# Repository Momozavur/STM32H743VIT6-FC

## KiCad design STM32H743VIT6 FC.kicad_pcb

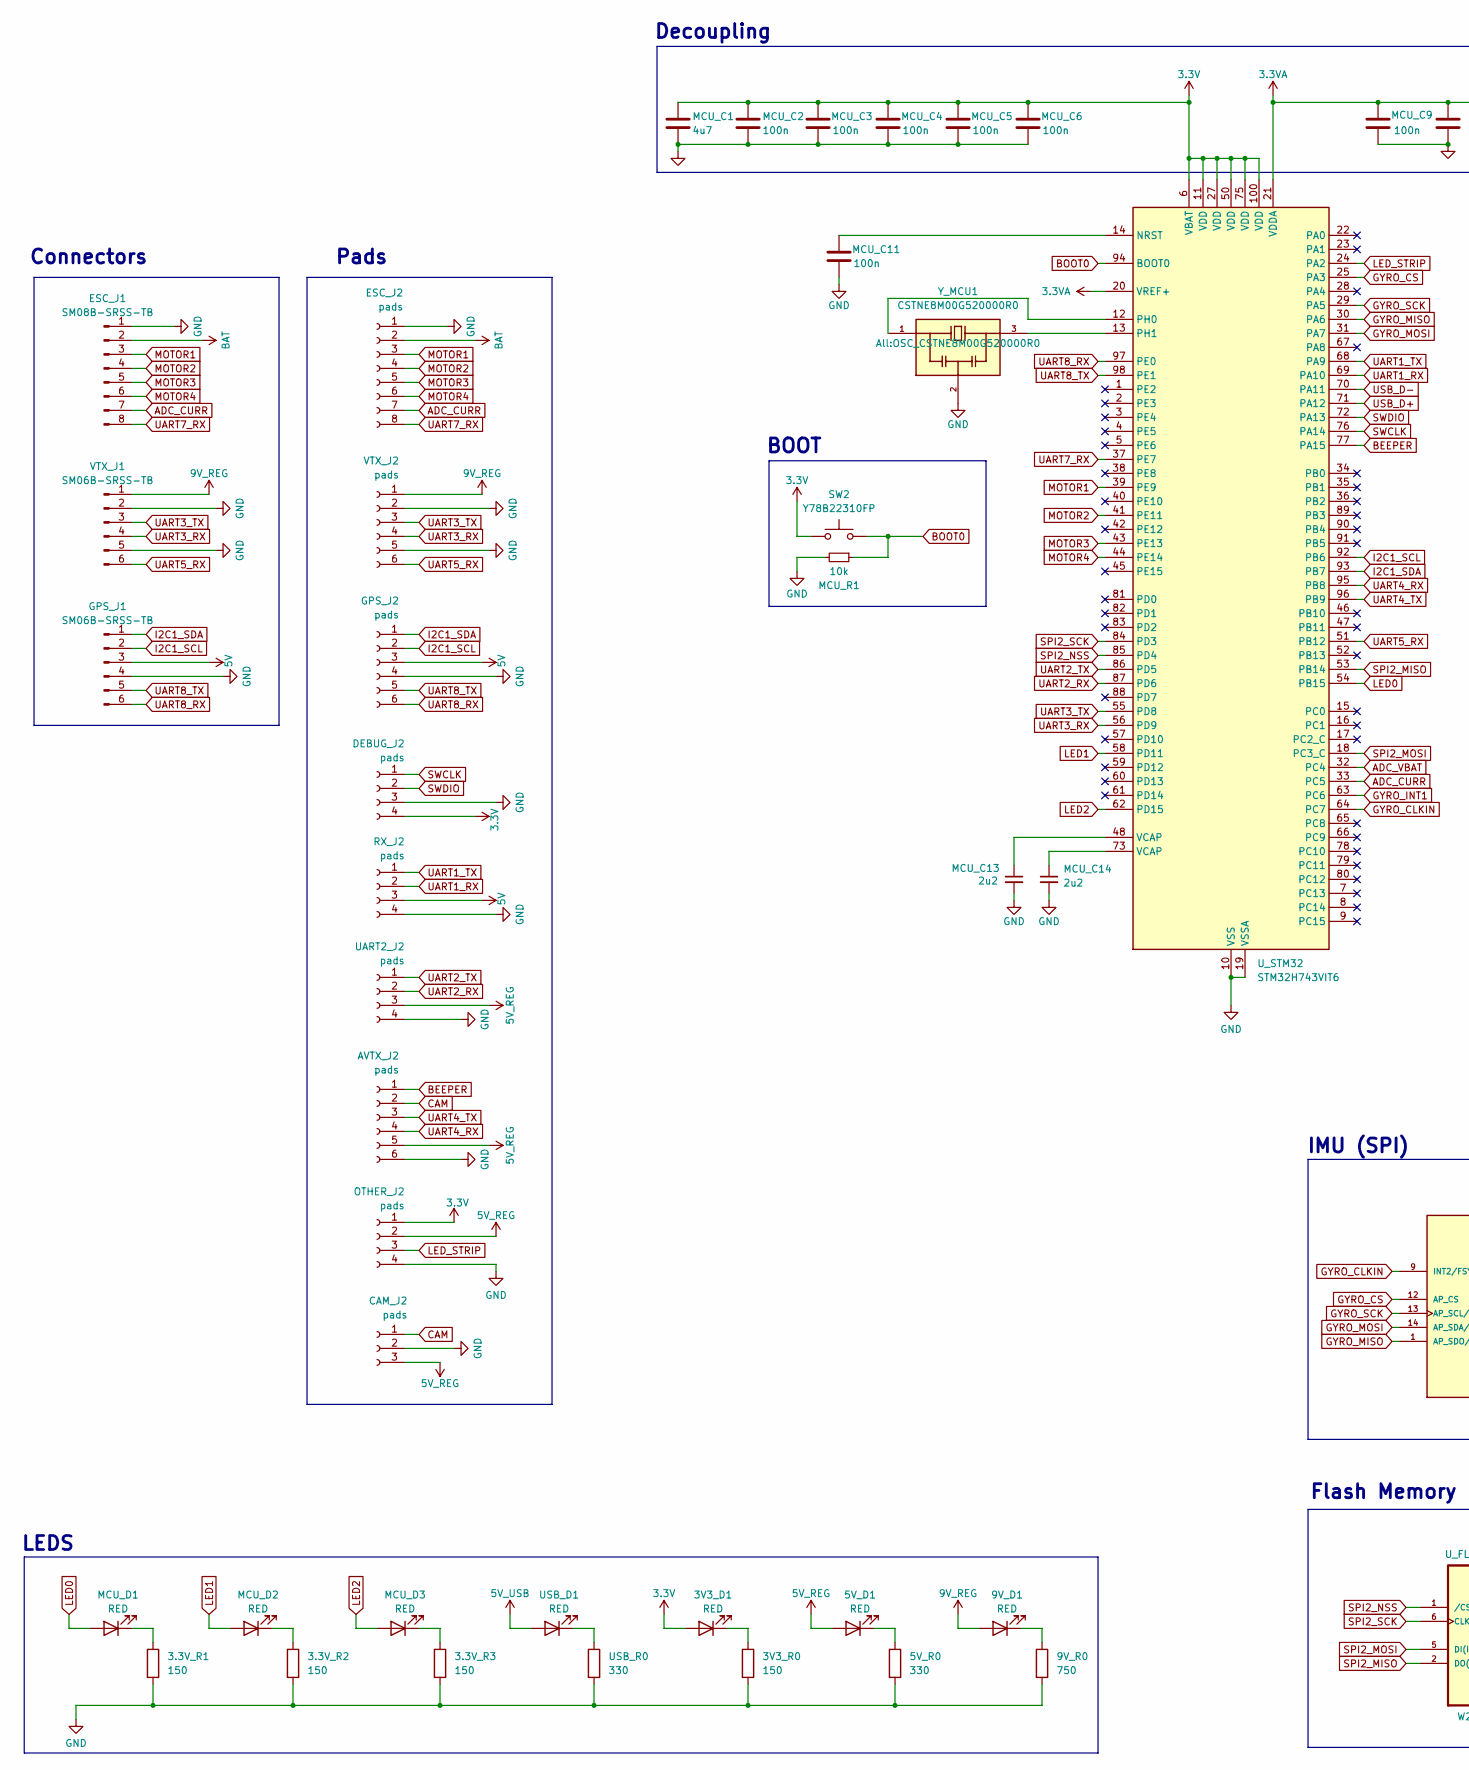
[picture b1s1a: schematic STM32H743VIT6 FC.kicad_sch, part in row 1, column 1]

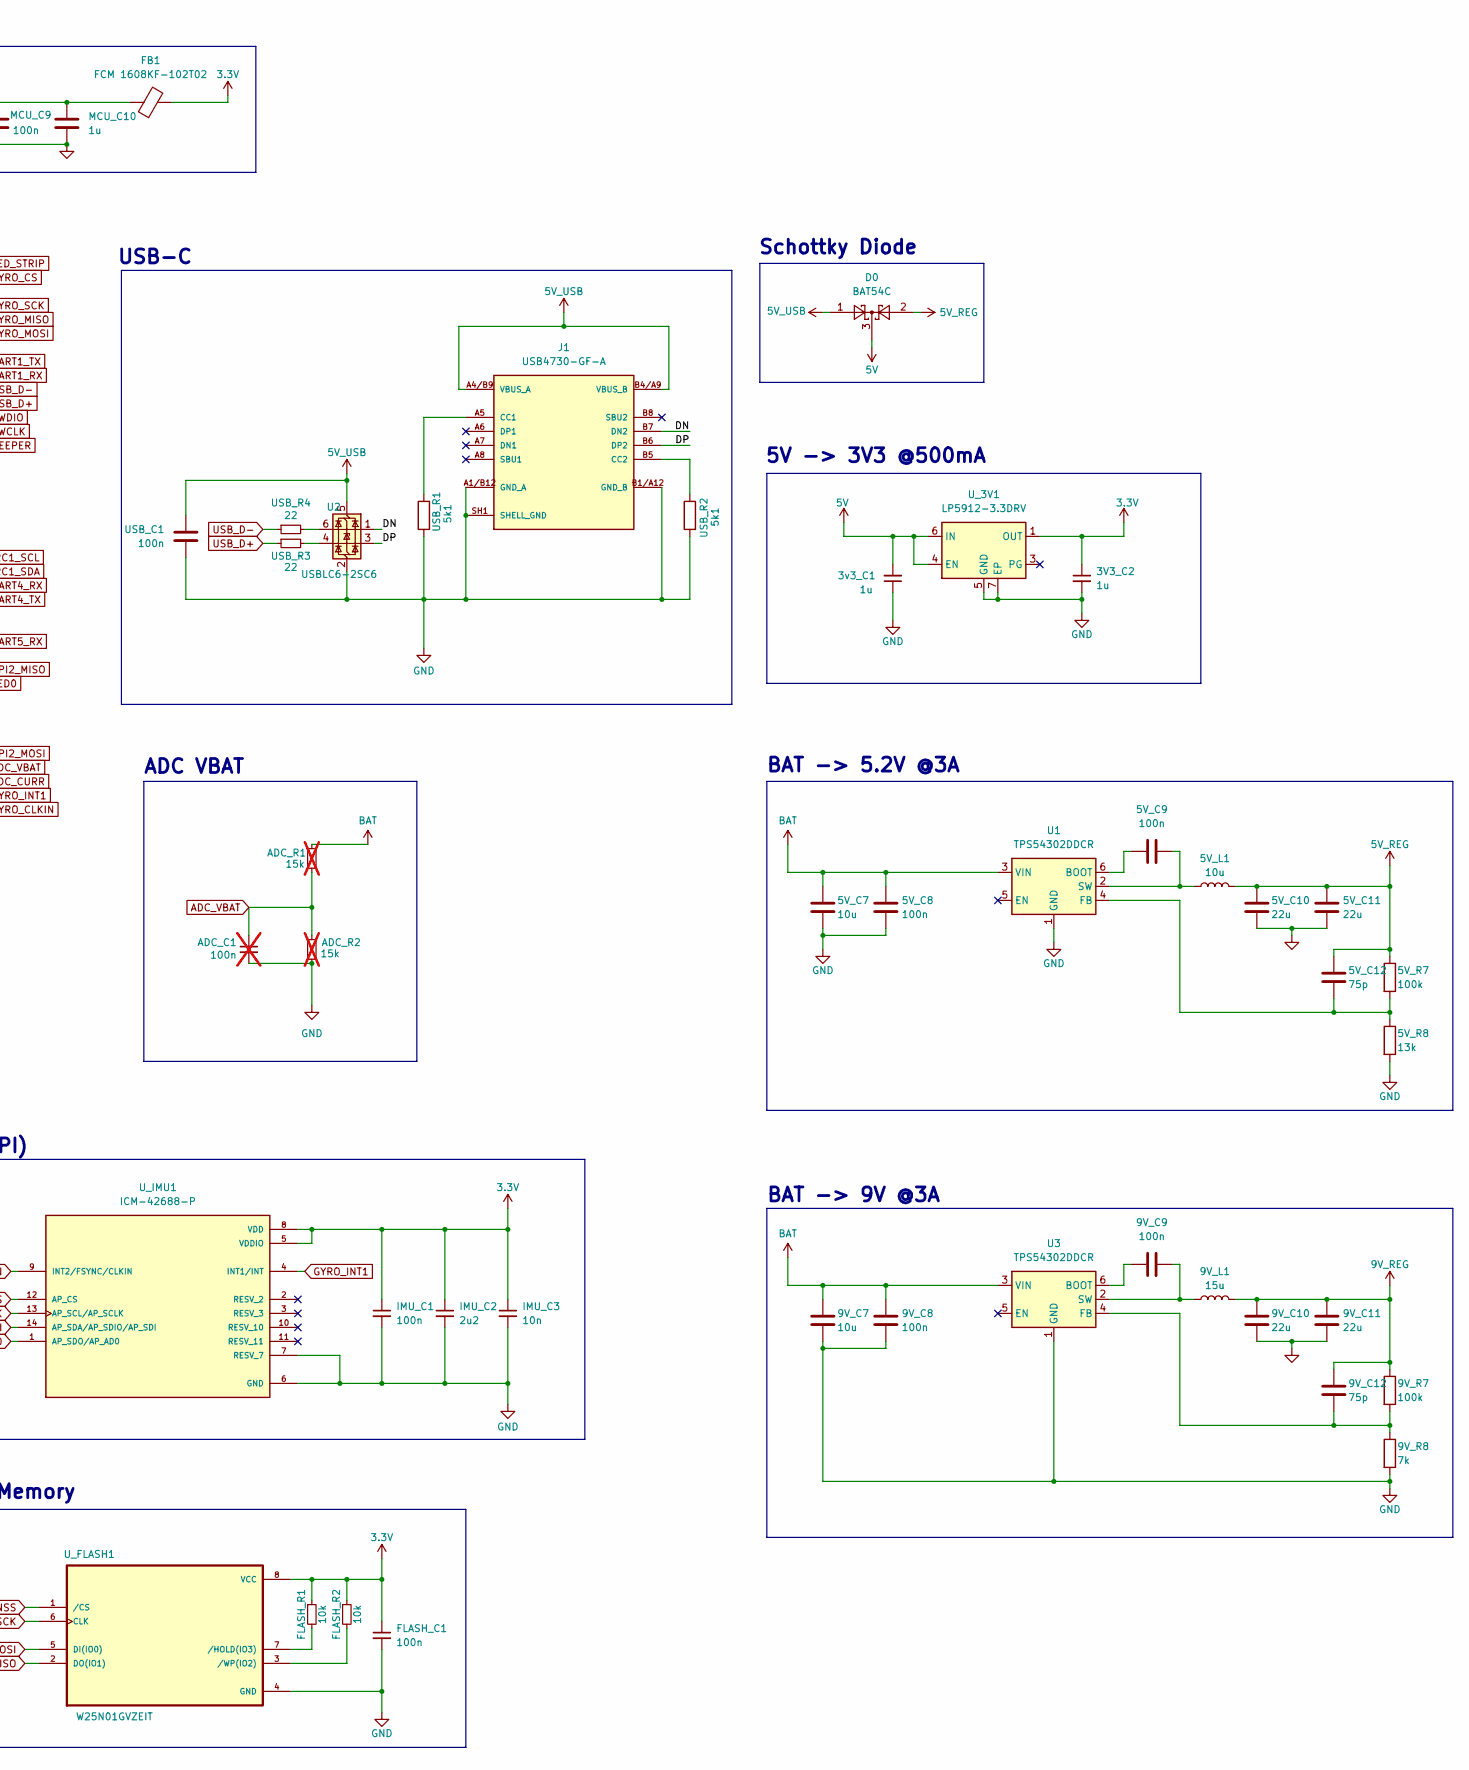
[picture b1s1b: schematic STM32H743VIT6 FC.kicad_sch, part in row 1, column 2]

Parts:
3.3V_R1, 3.3V_R2, 3.3V_R3, 3V3_R0: 150; R_0603_1608Metric_Pad0.98x0.95mm_HandSolder
3V3_C2, 3v3_C1: 1u; C_0603_1608Metric_Pad1.08x0.95mm_HandSolder
3V3_D1, 5V_D1, 9V_D1: RED; LED_0603_1608Metric_Pad1.05x0.95mm_HandSolder
5V_C7, 9V_C7: 10u; C_0603_1608Metric_Pad1.08x0.95mm_HandSolder
5V_C8, 5V_C9, 9V_C8, 9V_C9: 100n; C_0603_1608Metric_Pad1.08x0.95mm_HandSolder
5V_C10, 5V_C11, 9V_C10, 9V_C11: 22u; C_0603_1608Metric_Pad1.08x0.95mm_HandSolder
5V_C12, 9V_C12: 75p; C_0603_1608Metric_Pad1.08x0.95mm_HandSolder
5V_L1: 10u; L_Wuerth_MAPI-5030
5V_R0: 330; R_0603_1608Metric_Pad0.98x0.95mm_HandSolder
5V_R7, 9V_R7: 100k; R_0603_1608Metric_Pad0.98x0.95mm_HandSolder
5V_R8: 13k; R_0603_1608Metric_Pad0.98x0.95mm_HandSolder
9V_L1: 15u; L_Wuerth_MAPI-5030
9V_R0: 750; R_0603_1608Metric_Pad0.98x0.95mm_HandSolder
9V_R8: 7k; R_0603_1608Metric_Pad0.98x0.95mm_HandSolder
ADC_C1: 100n; C_0603_1608Metric_Pad1.08x0.95mm_HandSolder; not fitted
ADC_R1, ADC_R2: 15k; R_0603_1608Metric_Pad0.98x0.95mm_HandSolder; not fitted
AVTX_J2: pads; Pads_1x6
CAM_J2: pads; Pads_1x3
D0: BAT54C; SOT-23
DEBUG_J2: pads; Pads_1x4
ESC_J1: SM08B-SRSS-TB; SM08BSRSSTB
ESC_J2: pads; Pads_1x8
FB1: FCM 1608KF-102T02; R_0603_1608Metric_Pad0.98x0.95mm_HandSolder
FLASH_C1: 100n; C_0603_1608Metric_Pad1.08x0.95mm_HandSolder
FLASH_R1, FLASH_R2: 10k; R_0603_1608Metric_Pad0.98x0.95mm_HandSolder
GPS_J1: SM06B-SRSS-TB; SM06BSRSSTBLFSN
GPS_J2: pads; Pads_1x6
IMU_C1: 100n; C_0603_1608Metric_Pad1.08x0.95mm_HandSolder
IMU_C2: 2u2; C_0603_1608Metric_Pad1.08x0.95mm_HandSolder
IMU_C3: 10n; C_0603_1608Metric_Pad1.08x0.95mm_HandSolder
J1: USB4730-GF-A; GCT_USB4730-GF-A_REVA; PARTREV A
MCU_C1: 4u7; C_0603_1608Metric_Pad1.08x0.95mm_HandSolder
MCU_C2, MCU_C3, MCU_C4, MCU_C5, MCU_C6, MCU_C9, MCU_C11: 100n; C_0603_1608Metric_Pad1.08x0.95mm_HandSolder
MCU_C10: 1u; C_0603_1608Metric_Pad1.08x0.95mm_HandSolder; JLCPCB Part # C19666
MCU_C13, MCU_C14: 2u2; C_0603_1608Metric_Pad1.08x0.95mm_HandSolder
MCU_D1, MCU_D2, MCU_D3: RED; LED_0603_1608Metric_Pad1.05x0.95mm_HandSolder
MCU_R1: 10k; R_0603_1608Metric_Pad0.98x0.95mm_HandSolder; JLCPCB Part # C25744
OTHER_J2: pads; Pads_1x4
RX_J2: pads; Pads_1x4
SW2: Y78B22310FP; SW_SPST_PTS810; JLCPCB Part # C127488
U1, U3: TPS54302DDCR; SOT-23-6
U2: USBLC6-2SC6; SOT-23-6
UART2_J2: pads; Pads_1x4
USB_C1: 100n; C_0603_1608Metric_Pad1.08x0.95mm_HandSolder
USB_D1: RED; LED_0603_1608Metric_Pad1.05x0.95mm_HandSolder
USB_R0: 330; R_0603_1608Metric_Pad0.98x0.95mm_HandSolder
USB_R1, USB_R2: 5k1; R_0603_1608Metric_Pad0.98x0.95mm_HandSolder
USB_R3, USB_R4: 22; R_0603_1608Metric_Pad0.98x0.95mm_HandSolder
U_3V1: LP5912-3.3DRV; WSON-6-1EP_2x2mm_P0.65mm_EP1x1.6mm_ThermalVias
U_FLASH1: W25N01GVZEIT; SON127P600X800X80-9N
U_IMU1: ICM-42688-P; PQFN50P300X250X97-14N; PARTREV 1.2
U_STM32: STM32H743VIT6; LQFP-100_14x14mm_P0.5mm
VTX_J1: SM06B-SRSS-TB; SM06BSRSSTBLFSN
VTX_J2: pads; Pads_1x6
Y_MCU1: CSTNE8M00G520000R0; OSC_CSTNE8M00G520000R0; PARTREV JGC42-8858A

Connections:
3.3V: 3V3_C2.1, 3V3_D1.2 (A), DEBUG_J2.4, FB1.2, FLASH_C1.1, FLASH_R1.1, FLASH_R2.1, IMU_C1.1, IMU_C2.1, IMU_C3.1, MCU_C1.1, MCU_C2.1, MCU_C3.1, MCU_C4.1, MCU_C5.1, MCU_C6.1, OTHER_J2.1, SW2.2, U_3V1.1 (OUT), U_FLASH1.8 (VCC), U_IMU1.5 (VDDIO), U_IMU1.8 (VDD), U_STM32.6 (VBAT), U_STM32.11 (VDD), U_STM32.27 (VDD), U_STM32.50 (VDD), U_STM32.75 (VDD), U_STM32.100 (VDD)
3.3VA: FB1.1, MCU_C9.1, MCU_C10.1, U_STM32.20 (VREF+), U_STM32.21 (VDDA)
5V: 3v3_C1.2, D0.3, GPS_J1.3, GPS_J2.3, RX_J2.3, U_3V1.4 (EN), U_3V1.6 (IN)
5V_REG: 5V_C10.1, 5V_C11.1, 5V_C12.1, 5V_D1.2 (A), 5V_L1.2, 5V_R7.1, AVTX_J2.5, CAM_J2.3, D0.2, OTHER_J2.2, UART2_J2.3
5V_USB: D0.1, J1.A4/B9 (VBUS_A), J1.B4/A9 (VBUS_B), U2.5 (VBUS), USB_C1.2, USB_D1.2 (A)
9V_REG: 9V_C10.1, 9V_C11.1, 9V_C12.1, 9V_D1.2 (A), 9V_L1.2, 9V_R7.1, VTX_J1.1, VTX_J2.1
/DN: J1.B7 (DN2), U2.1 (I/O1)
/DP: J1.B6 (DP2), U2.3 (I/O2)
ADC_CURR: ESC_J1.7, ESC_J2.7, U_STM32.33 (PC5)
ADC_VBAT: ADC_C1.1, ADC_R1.2, ADC_R2.1, U_STM32.32 (PC4)
BAT: 5V_C7.1, 5V_C8.1, 9V_C7.1, 9V_C8.1, ADC_R1.1, ESC_J1.2, ESC_J2.2, U1.3 (VIN), U3.3 (VIN)
BEEPER: AVTX_J2.1, U_STM32.77 (PA15)
BOOT0: MCU_R1.1, SW2.1, U_STM32.94 (BOOT0)
CAM: AVTX_J2.2, CAM_J2.1
GND: 3.3V_R1.2, 3.3V_R2.2, 3.3V_R3.2, 3V3_C2.2, 3V3_R0.2, 3v3_C1.1, 5V_C7.2, 5V_C8.2, 5V_C10.2, 5V_C11.2, 5V_R0.2, 5V_R8.2, 9V_C7.2, 9V_C8.2, 9V_C10.2, 9V_C11.2, 9V_R0.2, 9V_R8.2, ADC_C1.2, ADC_R2.2, AVTX_J2.6, CAM_J2.2, DEBUG_J2.3, ESC_J1.1, ESC_J2.1, FLASH_C1.2, GPS_J1.4, GPS_J2.4, IMU_C1.2, IMU_C2.2, IMU_C3.2, J1.A1/B12 (GND_A), J1.B1/A12 (GND_B), J1.SH1 (SHELL_GND), J1.SH2 (SHELL_GND), J1.SH3 (SHELL_GND), J1.SH4 (SHELL_GND), MCU_C1.2, MCU_C2.2, MCU_C3.2, MCU_C4.2, MCU_C5.2, MCU_C6.2, MCU_C9.2, MCU_C10.2, MCU_C11.2, MCU_C13.2, MCU_C14.2, MCU_R1.2, OTHER_J2.4, RX_J2.4, U1.1 (GND), U2.2 (GND), U3.1 (GND), UART2_J2.4, USB_C1.1, USB_R0.2, USB_R1.1, USB_R2.2, U_3V1.5 (GND), U_3V1.7 (EP), U_FLASH1.4 (GND), U_FLASH1.9, U_IMU1.6 (GND), U_IMU1.7 (RESV_7), U_STM32.10 (VSS), U_STM32.19 (VSSA), U_STM32.26 (VSS), U_STM32.49 (VSS), U_STM32.74 (VSS), U_STM32.99 (VSS), VTX_J1.2, VTX_J1.5, VTX_J2.2, VTX_J2.5, Y_MCU1.2
GYRO_CLKIN: U_IMU1.9 (INT2/FSYNC/CLKIN), U_STM32.64 (PC7)
GYRO_CS: U_IMU1.12 (AP_CS), U_STM32.25 (PA3)
GYRO_INT1: U_IMU1.4 (INT1/INT), U_STM32.63 (PC6)
GYRO_MISO: U_IMU1.1 (AP_SDO/AP_AD0), U_STM32.30 (PA6)
GYRO_MOSI: U_IMU1.14 (AP_SDA/AP_SDIO/AP_SDI), U_STM32.31 (PA7)
GYRO_SCK: U_IMU1.13 (AP_SCL/AP_SCLK), U_STM32.29 (PA5)
I2C1_SCL: GPS_J1.2, GPS_J2.2, U_STM32.92 (PB6)
I2C1_SDA: GPS_J1.1, GPS_J2.1, U_STM32.93 (PB7)
LED0: MCU_D1.2 (A), U_STM32.54 (PB15)
LED1: MCU_D2.2 (A), U_STM32.58 (PD11)
LED2: MCU_D3.2 (A), U_STM32.62 (PD15)
LED_STRIP: OTHER_J2.3, U_STM32.24 (PA2)
MOTOR1: ESC_J1.3, ESC_J2.3, U_STM32.39 (PE9)
MOTOR2: ESC_J1.4, ESC_J2.4, U_STM32.41 (PE11)
MOTOR3: ESC_J1.5, ESC_J2.5, U_STM32.43 (PE13)
MOTOR4: ESC_J1.6, ESC_J2.6, U_STM32.44 (PE14)
unnamed: 3V3_D1.1 (K), 3V3_R0.1
unnamed: 5V_D1.1 (K), 5V_R0.1
unnamed: 9V_D1.1 (K), 9V_R0.1
unnamed: J1.A5 (CC1), USB_R1.2
unnamed: J1.B5 (CC2), USB_R2.1
unnamed: MCU_C13.1, U_STM32.48 (VCAP)
unnamed: MCU_C14.1, U_STM32.73 (VCAP)
unnamed: 3.3V_R1.1, MCU_D1.1 (K)
unnamed: 3.3V_R2.1, MCU_D2.1 (K)
unnamed: 3.3V_R3.1, MCU_D3.1 (K)
unnamed: 5V_C9.1, U1.6 (BOOT)
unnamed: 5V_C12.2, 5V_R7.2, 5V_R8.1, U1.4 (FB)
unnamed: 5V_C9.2, 5V_L1.1, U1.2 (SW)
unnamed: U2.6 (I/O1), USB_R4.2
unnamed: U2.4 (I/O2), USB_R3.2
unnamed: 9V_C9.1, U3.6 (BOOT)
unnamed: 9V_C12.2, 9V_R7.2, 9V_R8.1, U3.4 (FB)
unnamed: 9V_C9.2, 9V_L1.1, U3.2 (SW)
unnamed: USB_D1.1 (K), USB_R0.1
unnamed: FLASH_R1.2, U_FLASH1.7 (/HOLD(IO3))
unnamed: FLASH_R2.2, U_FLASH1.3 (/WP(IO2))
unnamed: MCU_C11.1, U_STM32.14 (NRST)
unnamed: U_STM32.12 (PH0), Y_MCU1.1
unnamed: U_STM32.13 (PH1), Y_MCU1.3
SPI2_MISO: U_FLASH1.2 (DO(IO1)), U_STM32.53 (PB14)
SPI2_MOSI: U_FLASH1.5 (DI(IO0)), U_STM32.18 (PC3_C)
SPI2_NSS: U_FLASH1.1 (/CS), U_STM32.85 (PD4)
SPI2_SCK: U_FLASH1.6 (CLK), U_STM32.84 (PD3)
SWCLK: DEBUG_J2.1, U_STM32.76 (PA14)
SWDIO: DEBUG_J2.2, U_STM32.72 (PA13)
UART1_RX: RX_J2.2, U_STM32.69 (PA10)
UART1_TX: RX_J2.1, U_STM32.68 (PA9)
UART2_RX: UART2_J2.2, U_STM32.87 (PD6)
UART2_TX: UART2_J2.1, U_STM32.86 (PD5)
UART3_RX: U_STM32.56 (PD9), VTX_J1.4, VTX_J2.4
UART3_TX: U_STM32.55 (PD8), VTX_J1.3, VTX_J2.3
UART4_RX: AVTX_J2.4, U_STM32.95 (PB8)
UART4_TX: AVTX_J2.3, U_STM32.96 (PB9)
UART5_RX: U_STM32.51 (PB12), VTX_J1.6, VTX_J2.6
UART7_RX: ESC_J1.8, ESC_J2.8, U_STM32.37 (PE7)
UART8_RX: GPS_J1.6, GPS_J2.6, U_STM32.97 (PE0)
UART8_TX: GPS_J1.5, GPS_J2.5, U_STM32.98 (PE1)
USB_D+: USB_R3.1, U_STM32.71 (PA12)
USB_D-: USB_R4.1, U_STM32.70 (PA11)

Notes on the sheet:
Flash Memory
LEDS
Connectors
5V -> 3V3 @500mA
BAT -> 5.2V @3A
Schottky Diode
Decoupling
ADC VBAT
IMU (SPI)
Pads
BOOT
USB-C
BAT -> 9V @3A

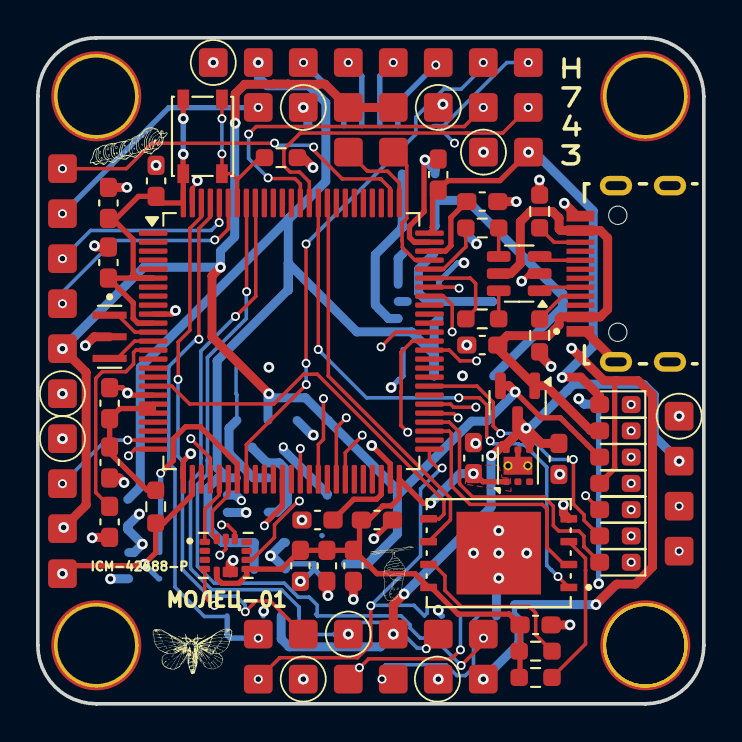
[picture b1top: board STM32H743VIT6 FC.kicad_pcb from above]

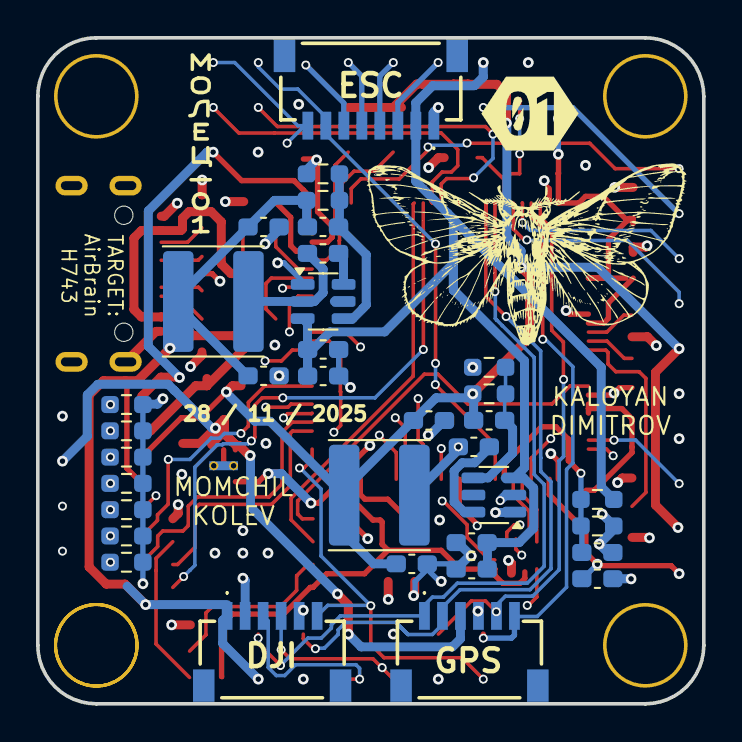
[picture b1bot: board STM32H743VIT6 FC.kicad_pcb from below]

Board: 4 copper layers, 37.0 x 37.0 mm, 89 parts (35 on the bottom side), 75 nets.

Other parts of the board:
H1, H2, H3, H4: MountingHole; MountingHole_4.3mm_M4_ISO14580_Pad_TopBottom
kibuzzard-692A4C78: G***; kibuzzard-692A4C78

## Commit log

2025-11-18 schematic
2025-11-18 AIRBRAINH743
2025-11-19 regulators
2025-11-19 boom boom
2025-11-19 labels
2025-11-19 power mux
2025-11-19 single sheet
2025-11-19 schottky
2025-11-19 mux no no no
2025-11-21 Verified and connected IMU.
2025-11-21 Verified baro, flash, and power. Added minimal pinout of the MCU.
2025-11-21 3.3V ldo
2025-11-21 W25N01GVZEIT
2025-11-23 Connected USB and fixed MCU decoupling.
2025-11-23 conns
2025-11-23 datasheets
2025-11-23 Added all pins from config and removed unused.
2025-11-24 led i buzzer
2025-11-24 Added auxiliary pads.
2025-11-24 frame
2025-11-24 Added footprints.
2025-11-24 Fixed imu and flash footprints.
2025-11-24 datasheet
2025-11-24 Added 3D models.
2025-11-24 pushhhh
2025-11-24 Fixed usb footprint.
2025-11-24 minor
2025-11-24 boom
2025-11-24 Board setup.
2025-11-24 posoki
2025-11-24 Restored IMU 3D.
2025-11-24 Restored other footprints too.
2025-11-24 Changed inductor and added net classes.
2025-11-24 Added second inductor.
2025-11-24 pads
2025-11-25 layout
2025-11-25 Removed EN resistors from bucks.
2025-11-25 regs
2025-11-25 leds
2025-11-25 muha
2025-11-26 Placed voltage regs and wired motors, gyro, and flash.
2025-11-26 more
2025-11-26 Moved 5V regulator.
2025-11-27 molec
2025-11-27 green
2025-11-28 Moved voltage divider back and wired uarts.
2025-11-28 blizo sme batkuu
2025-11-29 silk
2025-11-29 otnovo
2025-11-29 final
